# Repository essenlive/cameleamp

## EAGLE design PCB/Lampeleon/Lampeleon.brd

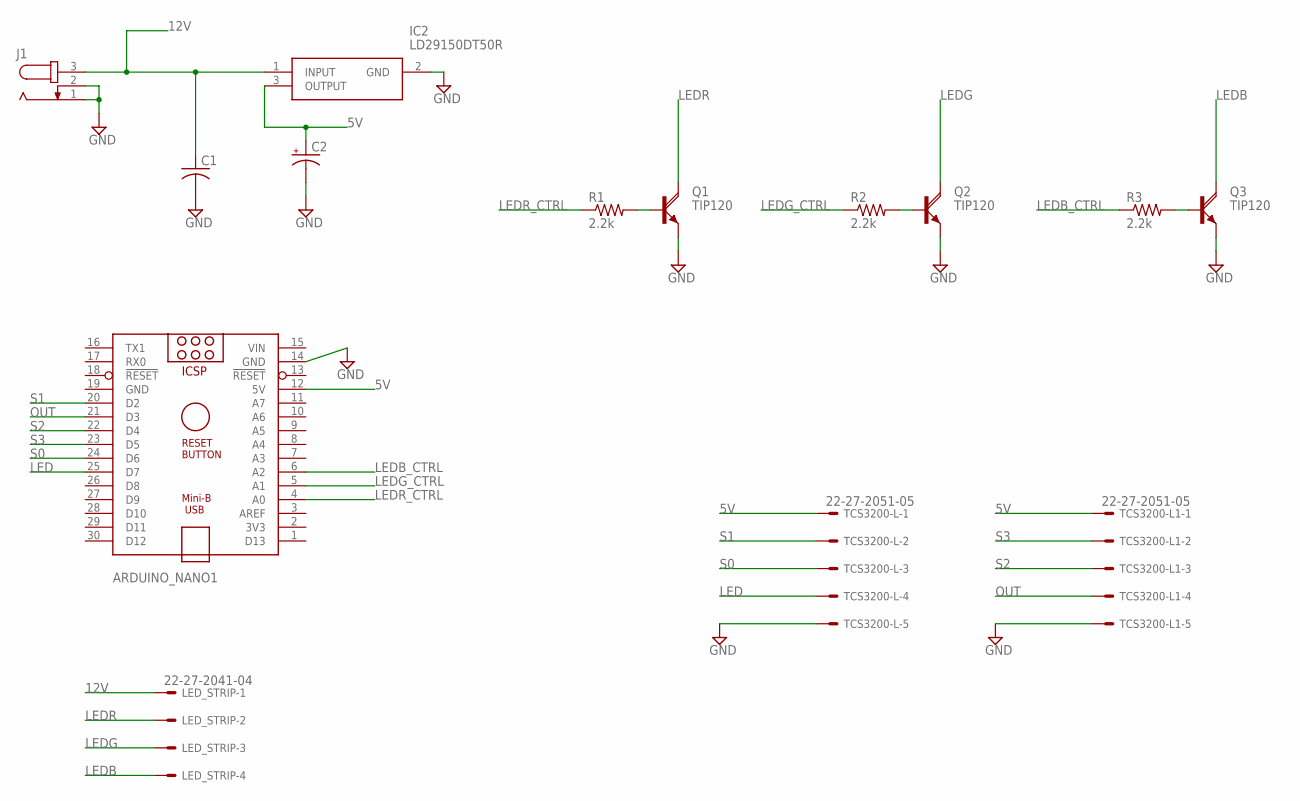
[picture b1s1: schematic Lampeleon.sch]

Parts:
ARDUINO_NANO1: ARDUINO_NANO
C1: C-US025-030X050; C025-030X050
C2: CPOL-USE2.5-5; E2,5-5
IC2: LD29150DT50R
J1: JACK-PLUG0; SPC4077
LED_STRIP: 22-27-2041-04; 6410-04
Q1, Q2, Q3: TIP120; TO220AH
R1, R2, R3: 2.2k; 0204/5
TCS3200-L, TCS3200-L1: 22-27-2051-05; 6410-05

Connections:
5V: ARDUINO_NANO1.12 (5V), C2.+, IC2.3 (OUTPUT), TCS3200-L.1, TCS3200-L1.1
12V: C1.1, IC2.1 (INPUT), J1.3, LED_STRIP.1
GND: ARDUINO_NANO1.14 (GND), ARDUINO_NANO1.19 (GND), C1.2, C2.-, IC2.2 (GND), J1.1, J1.2, Q1.E, Q2.E, Q3.E, TCS3200-L.5, TCS3200-L1.5
LED: ARDUINO_NANO1.25 (D7), TCS3200-L.4
LEDB: LED_STRIP.4, Q3.C
LEDB_CTRL: ARDUINO_NANO1.6 (A2), R3.1
LEDG: LED_STRIP.3, Q2.C
LEDG_CTRL: ARDUINO_NANO1.5 (A1), R2.1
LEDR: LED_STRIP.2, Q1.C
LEDR_CTRL: ARDUINO_NANO1.4 (A0), R1.1
unnamed: Q2.B, R2.2
unnamed: Q1.B, R1.2
unnamed: Q3.B, R3.2
OUT: ARDUINO_NANO1.21 (D3), TCS3200-L1.4
S0: ARDUINO_NANO1.24 (D6), TCS3200-L.3
S1: ARDUINO_NANO1.20 (D2), TCS3200-L.2
S2: ARDUINO_NANO1.22 (D4), TCS3200-L1.3
S3: ARDUINO_NANO1.23 (D5), TCS3200-L1.2
VIN: ARDUINO_NANO1.15 (VIN)

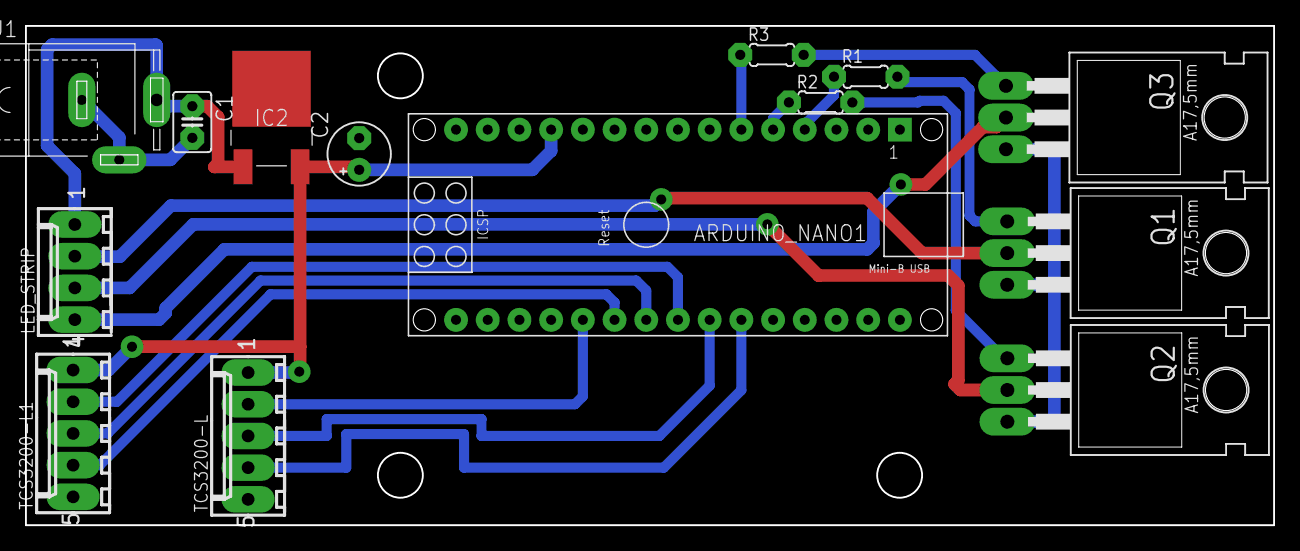
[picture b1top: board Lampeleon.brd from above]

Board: 2 copper layers, 100.0 x 40.0 mm, 14 parts (0 on the bottom side), 18 nets.

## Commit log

2021-04-28 📝Added blink example placeholder
2021-05-11 ⚡Added simple color loop
2021-05-11 🎨Added basic color sensing component
2021-06-29 ⚡Added PCB and scematic files
